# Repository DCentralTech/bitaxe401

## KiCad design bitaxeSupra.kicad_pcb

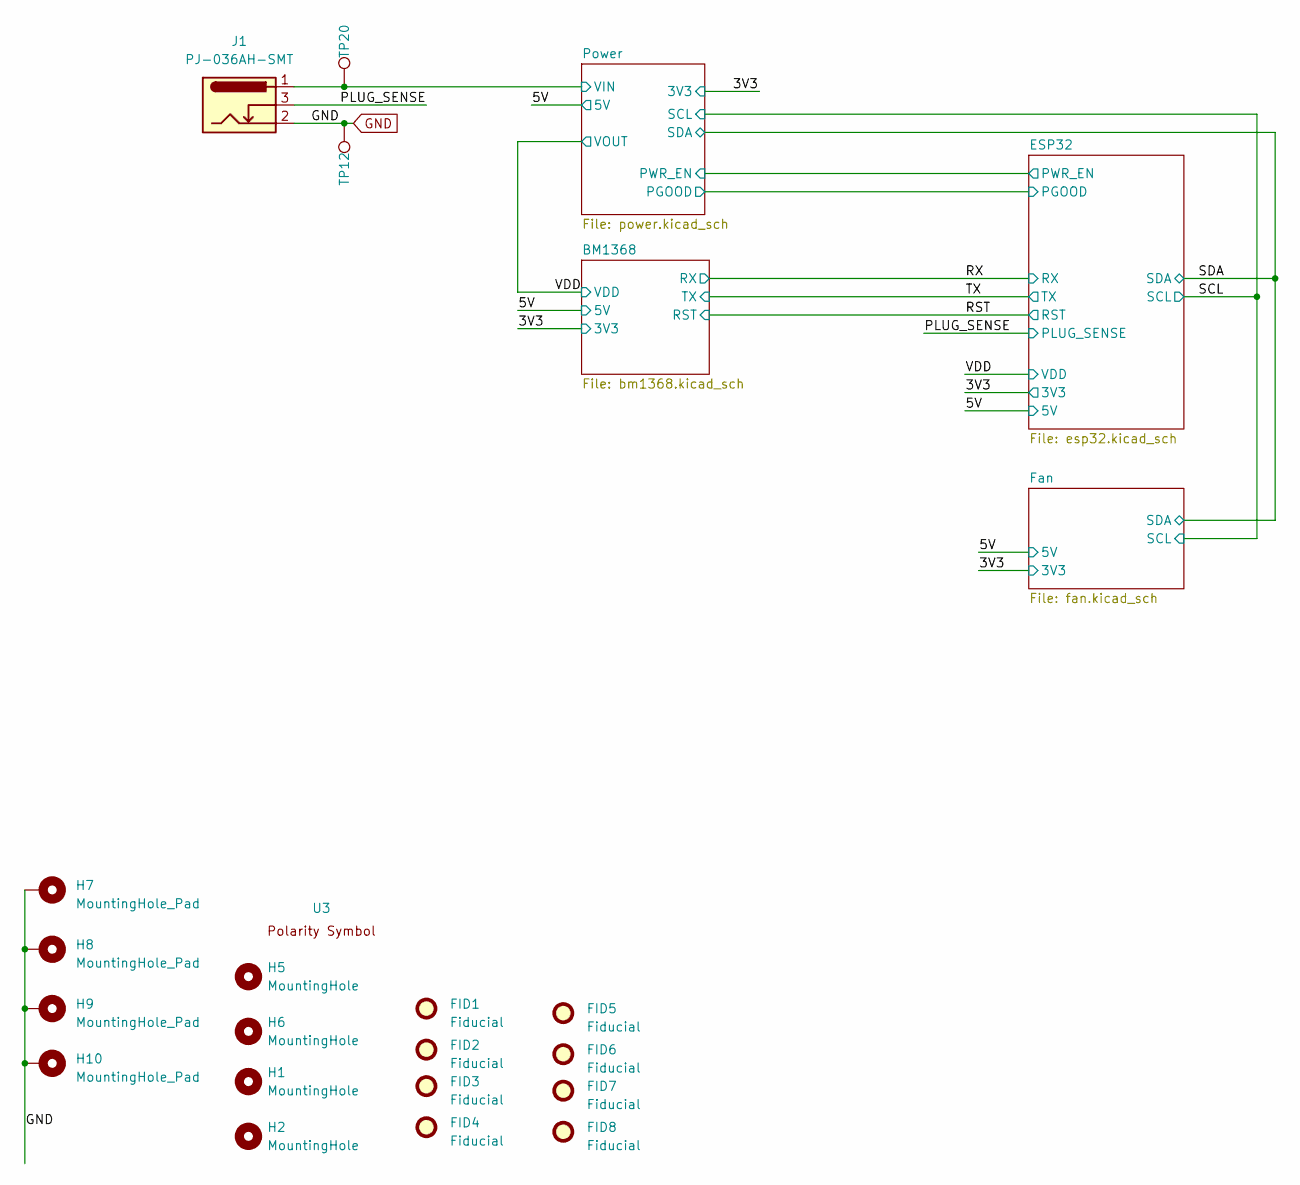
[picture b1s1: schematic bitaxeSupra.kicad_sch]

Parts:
FID1, FID2, FID3, FID4, FID5, FID6, FID7, FID8: Fiducial; Fiducial_1mm_Mask2mm
H1, H2, H5, H6: MountingHole; MountingHole_3.5mm
H7, H8, H9, H10: MountingHole_Pad; MountingHole_3mm_Pad_Via
J1: PJ-036AH-SMT; BarrelJack_CUI_PJ-036AH-SMT_Horizontal; PARTNO PJ-036AH-SMT; JLCPCB #1 C9900024875
TP12, TP20: TestPoint; TestPoint_Pad_D3.0mm
U3: polarity

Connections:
/PLUG_SENSE: J1.3; also elsewhere on the board
/Power/VIN: J1.1, TP20.1; also elsewhere on the board
GND: H7.1, H8.1, H9.1, H10.1, J1.2, TP12.1; also elsewhere on the board

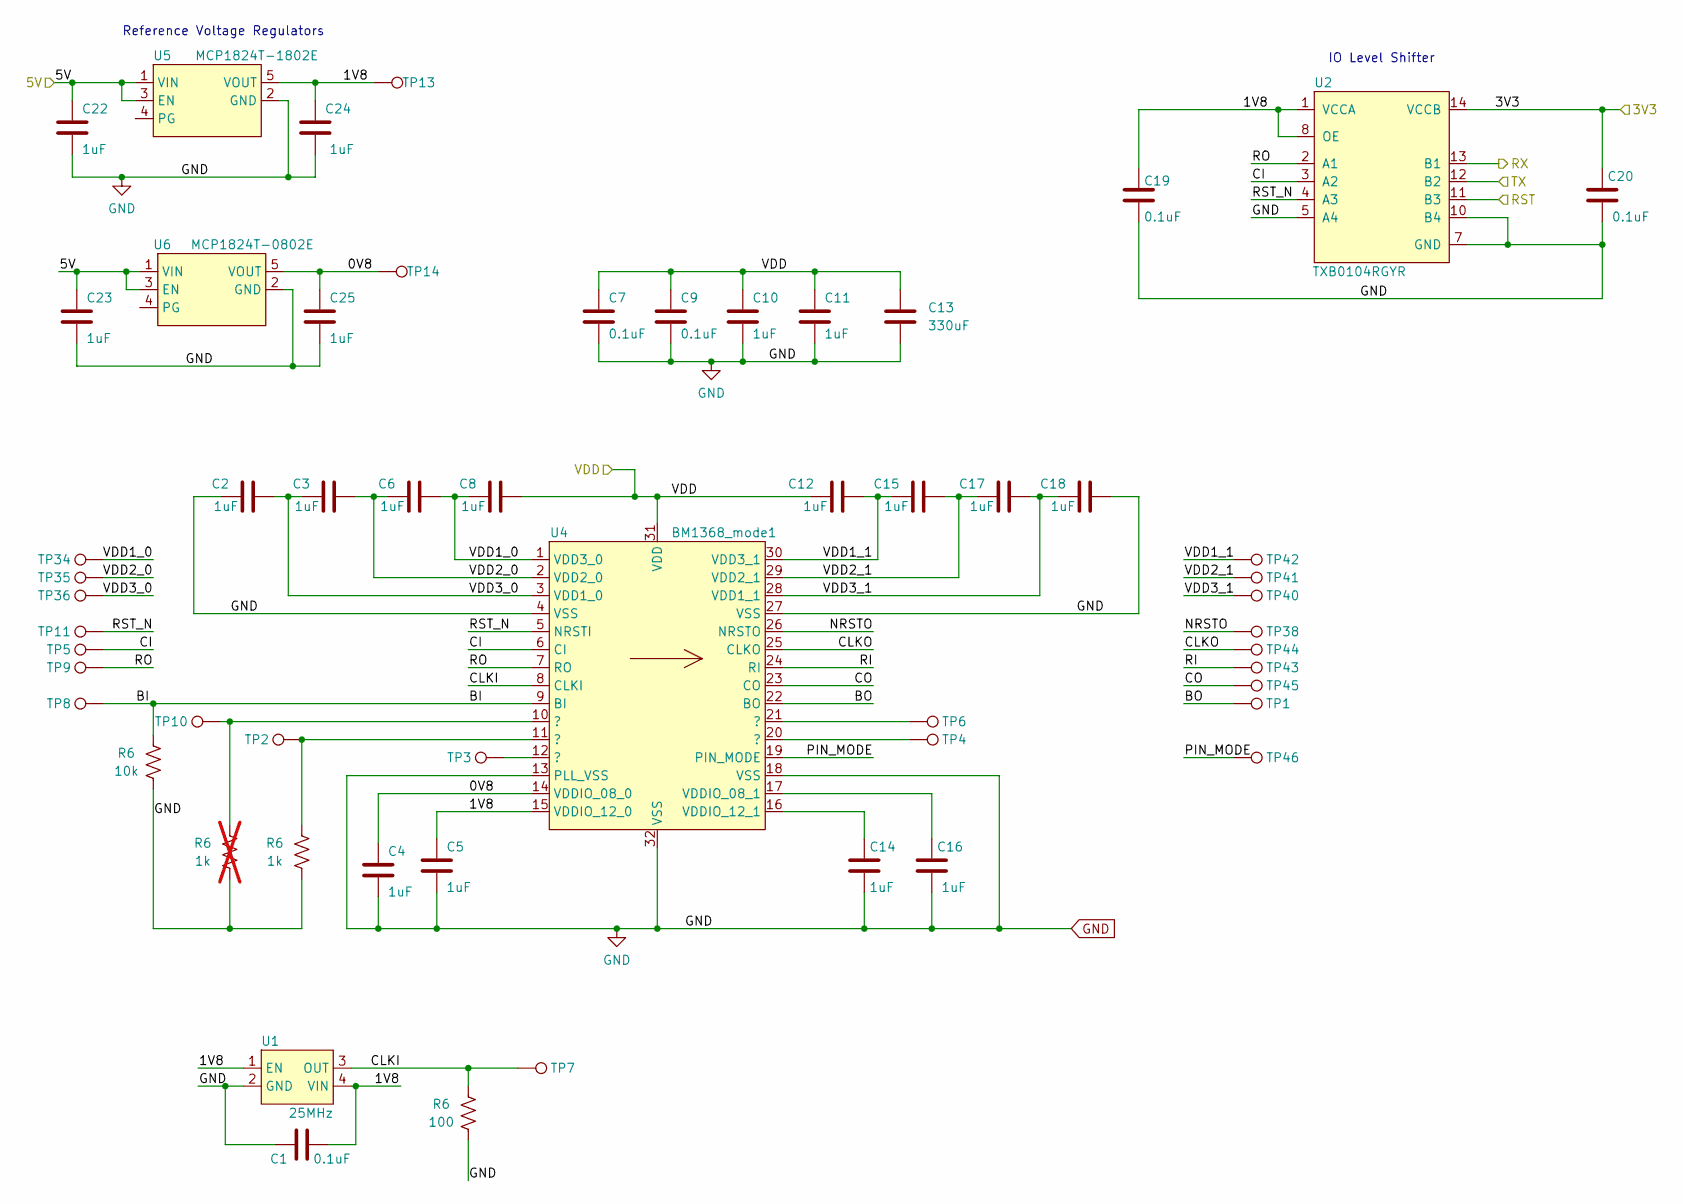
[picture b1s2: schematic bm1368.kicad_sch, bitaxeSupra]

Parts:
C1, C7, C9, C19, C20: 0.1uF; C_0402_1005Metric; PARTNO 0402X104K100CT; JLCPCB #1 C129131
C2, C3, C4, C5, C6, C8, C10, C11, C12, C14, C15, C16, C17, C18, C22, C23, C24, C25: 1uF; C_0402_1005Metric; PARTNO EMK105BJ105MV-F; JLCPCB #1 C325464
C13: 330uF; C_1210_3225Metric; PARTNO GRM32ER60G337ME05L; JLCPCB #1 C528969
R6: 1k; R_0402_1005Metric; PARTNO RC0402FR-071KL; JLCPCB #1 C106235; not fitted
TP1, TP2, TP3, TP4, TP5, TP6, TP7, TP8, TP9, TP10, TP11, TP13, TP14, TP34, TP35, TP36, TP38, TP40, TP41, TP42, TP43, TP44, TP45, TP46: TestPoint; TestPoint_Pad_D1.5mm
U1: 25MHz; O 25,0-JO32-B-1V3-1-T1-LF; PARTNO O 25,0-JO32-B-1V3-1-T1-LF; JLCPCB #1 C669088
U2: TXB0104RGYR; TXB0104; PARTNO TXB0104RGYR; JLCPCB #1 C400708
U4: BM1368_mode1; BM1368
U5: MCP1824T-1802E; SOT-23-5; PARTNO MCP1824T-1802E/OT; JLCPCB #1 C625462
U6: MCP1824T-0802E; SOT-23-5; PARTNO MCP1824T-0802E/OT; JLCPCB #1 C625460

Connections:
/3V3: C20.1, U2.14 (VCCB); also elsewhere on the board
/5V: C22.1, C23.1, U5.1 (VIN), U5.3 (EN), U6.1 (VIN), U6.3 (EN); also elsewhere on the board
/BM1368/0V8: C4.1, C25.1, TP14.1, U4.14 (VDDIO_08_0), U6.5 (VOUT)
/BM1368/1V8: C1.2, C5.1, C19.1, C24.1, TP13.1, U1.1 (EN), U1.4 (VIN), U2.1 (VCCA), U2.8 (OE), U4.15 (VDDIO_12_0), U5.5 (VOUT)
/BM1368/BO: TP1.1, U4.22 (BO)
/BM1368/CI: TP5.1, U2.3 (A2), U4.6 (CI)
/BM1368/CLKO: TP44.1, U4.25 (CLKO)
/BM1368/CO: TP45.1, U4.23 (CO)
/BM1368/NRSTO: TP38.1, U4.26 (NRSTO)
/BM1368/PIN_MODE: TP46.1, U4.19 (PIN_MODE)
/BM1368/RI: TP43.1, U4.24 (RI)
/BM1368/RO: TP9.1, U2.2 (A1), U4.7 (RO)
/BM1368/RST_N: TP11.1, U2.4 (A3), U4.5 (NRSTI)
/BM1368/VDD1_0: C6.2, C8.1, TP34.1, U4.1 (VDD3_0)
/BM1368/VDD1_1: C12.2, C15.1, TP42.1, U4.30 (VDD3_1)
/BM1368/VDD2_0: C3.2, C6.1, TP35.1, U4.2 (VDD2_0)
/BM1368/VDD2_1: C15.2, C17.1, TP41.1, U4.29 (VDD2_1)
/BM1368/VDD3_0: C2.2, C3.1, TP36.1, U4.3 (VDD1_0)
/BM1368/VDD3_1: C17.2, C18.1, TP40.1, U4.28 (VDD1_1)
/RST: U2.11 (B3); also elsewhere on the board
/RX: U2.13 (B1); also elsewhere on the board
/TX: U2.12 (B2); also elsewhere on the board
/VDD: C7.1, C8.2, C9.1, C10.1, C11.1, C12.1, C13.1, U4.31 (VDD); also elsewhere on the board
GND: C1.1, C2.1, C4.2, C5.2, C7.2, C9.2, C10.2, C11.2, C13.2, C14.2, C16.2, C18.2, C19.2, C20.2, C22.2, C23.2, C24.2, C25.2, R6.1, U1.2 (GND), U2.5 (A4), U2.7 (GND), U2.10 (B4), U2.15 (GND), U2.16 (GND), U2.17 (GND), U2.18 (GND), U2.19 (GND), U4.4 (VSS), U4.13 (PLL_VSS), U4.18 (VSS), U4.27 (VSS), U4.32 (VSS), U5.2 (GND), U6.2 (GND); also elsewhere on the board
unnamed: TP3.1, U4.12 (?)
unnamed: TP4.1, U4.20 (?)
unnamed: TP6.1, U4.21 (?)
unnamed: C16.1, U4.17 (VDDIO_08_1)
unnamed: C14.1, U4.16 (VDDIO_12_1)

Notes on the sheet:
Reference Voltage Regulators
IO Level Shifter

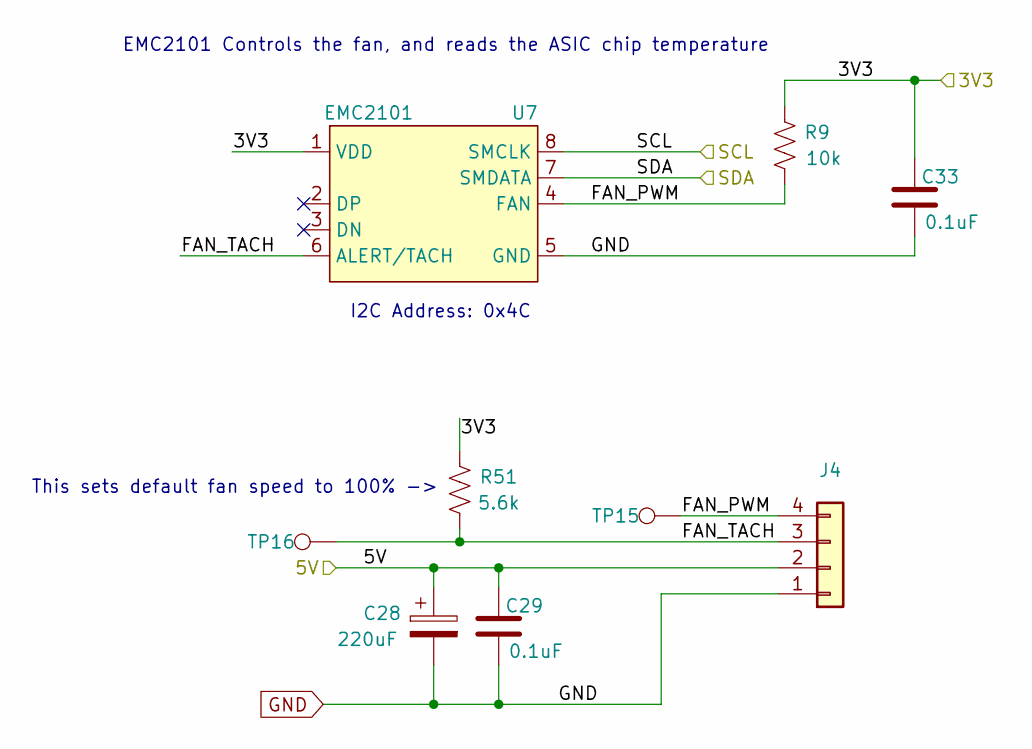
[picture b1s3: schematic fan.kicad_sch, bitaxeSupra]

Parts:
C28: 220uF; CP_Elec_6.3x7.7; PARTNO 865080345012; JLCPCB #1 C88742
C29, C33: 0.1uF; C_0402_1005Metric; PARTNO 0402X104K100CT; JLCPCB #1 C129131
J4: Conn_01x04; 470531000; PARTNO 470531000; JLCPCB #1 C492453
R9: 10k; R_0402_1005Metric; PARTNO RC0402JR-0710KL; JLCPCB #1 C60489
R51: 5.6k; R_0402_1005Metric; PARTNO RC0402FR-135K6L; JLCPCB #1 C409701
TP15, TP16: TestPoint; TestPoint_Pad_D1.5mm
U7: EMC2101; TSSOP-8_3x3mm_P0.65mm; PARTNO EMC2101-R-ACZL-TR; JLCPCB #1 C626968

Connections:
/3V3: C33.1, R9.2, U7.1 (VDD); also elsewhere on the board
/5V: C28.1, C29.1, J4.2; also elsewhere on the board
/Fan/FAN_PWM: J4.4, R9.1, TP15.1, U7.4 (FAN); also elsewhere on the board
/Fan/FAN_TACH: J4.3, TP16.1, U7.6 (ALERT/TACH); also elsewhere on the board
/SCL: U7.8 (SMCLK); also elsewhere on the board
/SDA: U7.7 (SMDATA); also elsewhere on the board
GND: C28.2, C29.2, C33.2, J4.1, U7.5 (GND); also elsewhere on the board

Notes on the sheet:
EMC2101 Controls the fan, and reads the ASIC chip temperature
This sets default fan speed to 100% ->
I2C Address: 0x4C

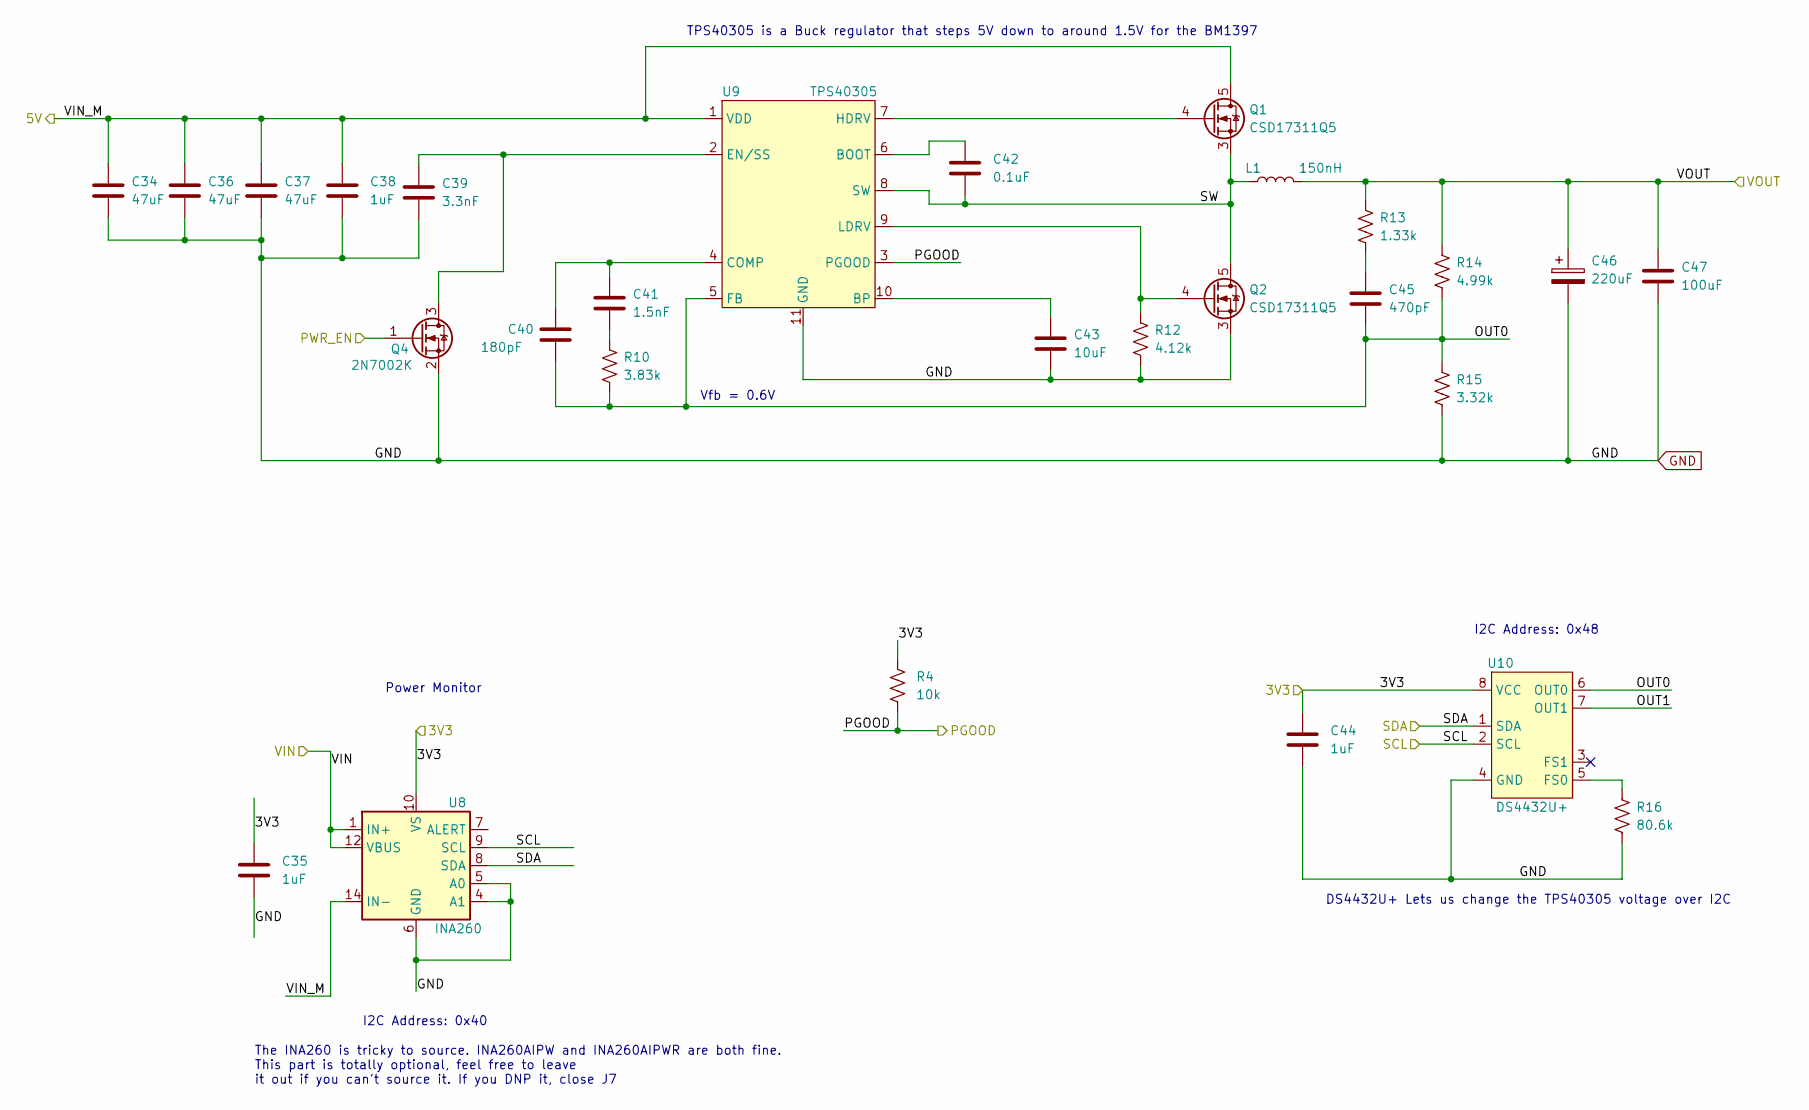
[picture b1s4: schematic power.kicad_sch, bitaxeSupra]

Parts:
C34, C36, C37: 47uF; C_1210_3225Metric; PARTNO GRM32ER61C476KE15L; JLCPCB #1 C77101
C35, C44: 1uF; C_0402_1005Metric; PARTNO EMK105BJ105MV-F; JLCPCB #1 C325464
C38: 1uF; C_0805_2012Metric; PARTNO CL21B105KOFNNNG; JLCPCB #1 C24123
C39: 3.3nF; C_0402_1005Metric; PARTNO CL05B332KB5NNNC; JLCPCB #1 C26404
C40: 180pF; C_0805_2012Metric; PARTNO CC0805JRNPO9BN181; JLCPCB #1 C458933
C41: 1.5nF; C_0805_2012Metric; PARTNO CC0805KRX7R9BB152; JLCPCB #1 C107142
C42: 0.1uF; C_0402_1005Metric; PARTNO 0402X104K100CT; JLCPCB #1 C129131
C43: 10uF; C_0805_2012Metric; PARTNO CL21A106KOQNNNE; JLCPCB #1 C1713
C45: 470pF; C_0805_2012Metric; PARTNO 0805B471K500CT; JLCPCB #1 C338123
C46: 220uF; CAP_2R5TPE220MAFB; PARTNO 2R5TPE220MAFB; JLCPCB #1 C909691
C47: 100uF; C_1206_3216Metric; PARTNO C3216X5R0J107M160AB; JLCPCB #1 C242097
L1: 150nH; FP1005R1-R15-R; PARTNO FP1005R1-R15-R; JLCPCB #1 C2923790
Q1, Q2: CSD17311Q5; PARTNO CSD17311Q5; JLCPCB #1 C139640
Q4: 2N7002K; SOT-323_SC-70; PARTNO 2N7002KW; JLCPCB #1 C266797
R4: 10k; R_0402_1005Metric; PARTNO RC0402JR-0710KL; JLCPCB #1 C60489
R10: 3.83k; R_0402_1005Metric; PARTNO RC0402FR-073K83L; JLCPCB #1 C67236
R12: 4.12k; R_0402_1005Metric; PARTNO RMCF0402FT4K12; JLCPCB #1 C60081
R13: 1.33k; R_0402_1005Metric; PARTNO RC0402FR-071K33L; JLCPCB #1 C226848
R14: 4.99k; R_0402_1005Metric; PARTNO RC0402FR-074K99L; JLCPCB #1 C25903
R15: 3.32k; R_0402_1005Metric; PARTNO RC0402FR-073K32L; JLCPCB #1 C60075
R16: 80.6k; R_0402_1005Metric; PARTNO RC0402FR-0780K6L; JLCPCB #1 C155698
U8: INA260; TSSOP-16_4.4x5mm_P0.65mm; PARTNO INA260AIPW; JLCPCB #1 C2155885
U9: TPS40305; PARTNO TPS40305DRCR; JLCPCB #1 C140285
U10: DS4432U+; TSSOP-8_3x3mm_P0.65mm; PARTNO DS4432U+; JLCPCB #1 C2679620

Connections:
/3V3: C35.1, C44.1, R4.1, U8.10 (VS), U10.8 (VCC); also elsewhere on the board
/5V: C34.1, C36.1, C37.1, C38.1, Q1.5 (D), U8.14 (IN-), U8.15 (IN-), U8.16 (IN-), U9.1 (VDD); also elsewhere on the board
/ESP32/PWR_EN: Q4.1 (G); also elsewhere on the board
/Power/OUT0: C40.2, C45.2, R10.2, R14.2, R15.1, U9.5 (FB), U10.6 (OUT0)
/Power/OUT1: U10.7 (OUT1)
/Power/PGOOD: R4.2, U9.3 (PGOOD); also elsewhere on the board
/Power/SW: C42.2, L1.1, Q1.1, Q1.2, Q1.3 (S), Q2.5 (D), U9.8 (SW)
/Power/VIN: U8.1 (IN+), U8.2 (IN+), U8.3 (IN+), U8.12 (VBUS); also elsewhere on the board
/SCL: U8.9 (SCL), U10.2 (SCL); also elsewhere on the board
/SDA: U8.8 (SDA), U10.1 (SDA); also elsewhere on the board
/VDD: C46.1, C47.1, L1.2, R13.1, R14.1; also elsewhere on the board
GND: C34.2, C35.2, C36.2, C37.2, C38.2, C39.2, C43.2, C44.2, C46.2, C47.2, Q2.1, Q2.2, Q2.3 (S), Q4.2 (S), R12.2, R15.2, R16.2, U8.4 (A1), U8.5 (A0), U8.6 (GND), U8.11 (GND), U9.11 (GND), U10.4 (GND); also elsewhere on the board
unnamed: C41.2, R10.1
unnamed: C45.1, R13.2
unnamed: Q1.4 (G), U9.7 (HDRV)
unnamed: Q2.4 (G), R12.1, U9.9 (LDRV)
unnamed: C39.1, Q4.3 (D), U9.2 (EN/SS)
unnamed: C42.1, U9.6 (BOOT)
unnamed: C43.1, U9.10 (BP)
unnamed: C40.1, C41.1, U9.4 (COMP)
unnamed: R16.1, U10.5 (FS0)

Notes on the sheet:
DS4432U+ Lets us change the TPS40305 voltage over I2C
I2C Address: 0x48
The INA260 is tricky to source. INA260AIPW and INA260AIPWR are both fine. This part is totally optional, feel free to leave it out if you can't source it. If you DNP it, close J7
Power Monitor
TPS40305 is a Buck regulator that steps 5V down to around 1.5V for the BM1397
I2C Address: 0x40
Vfb = 0.6V

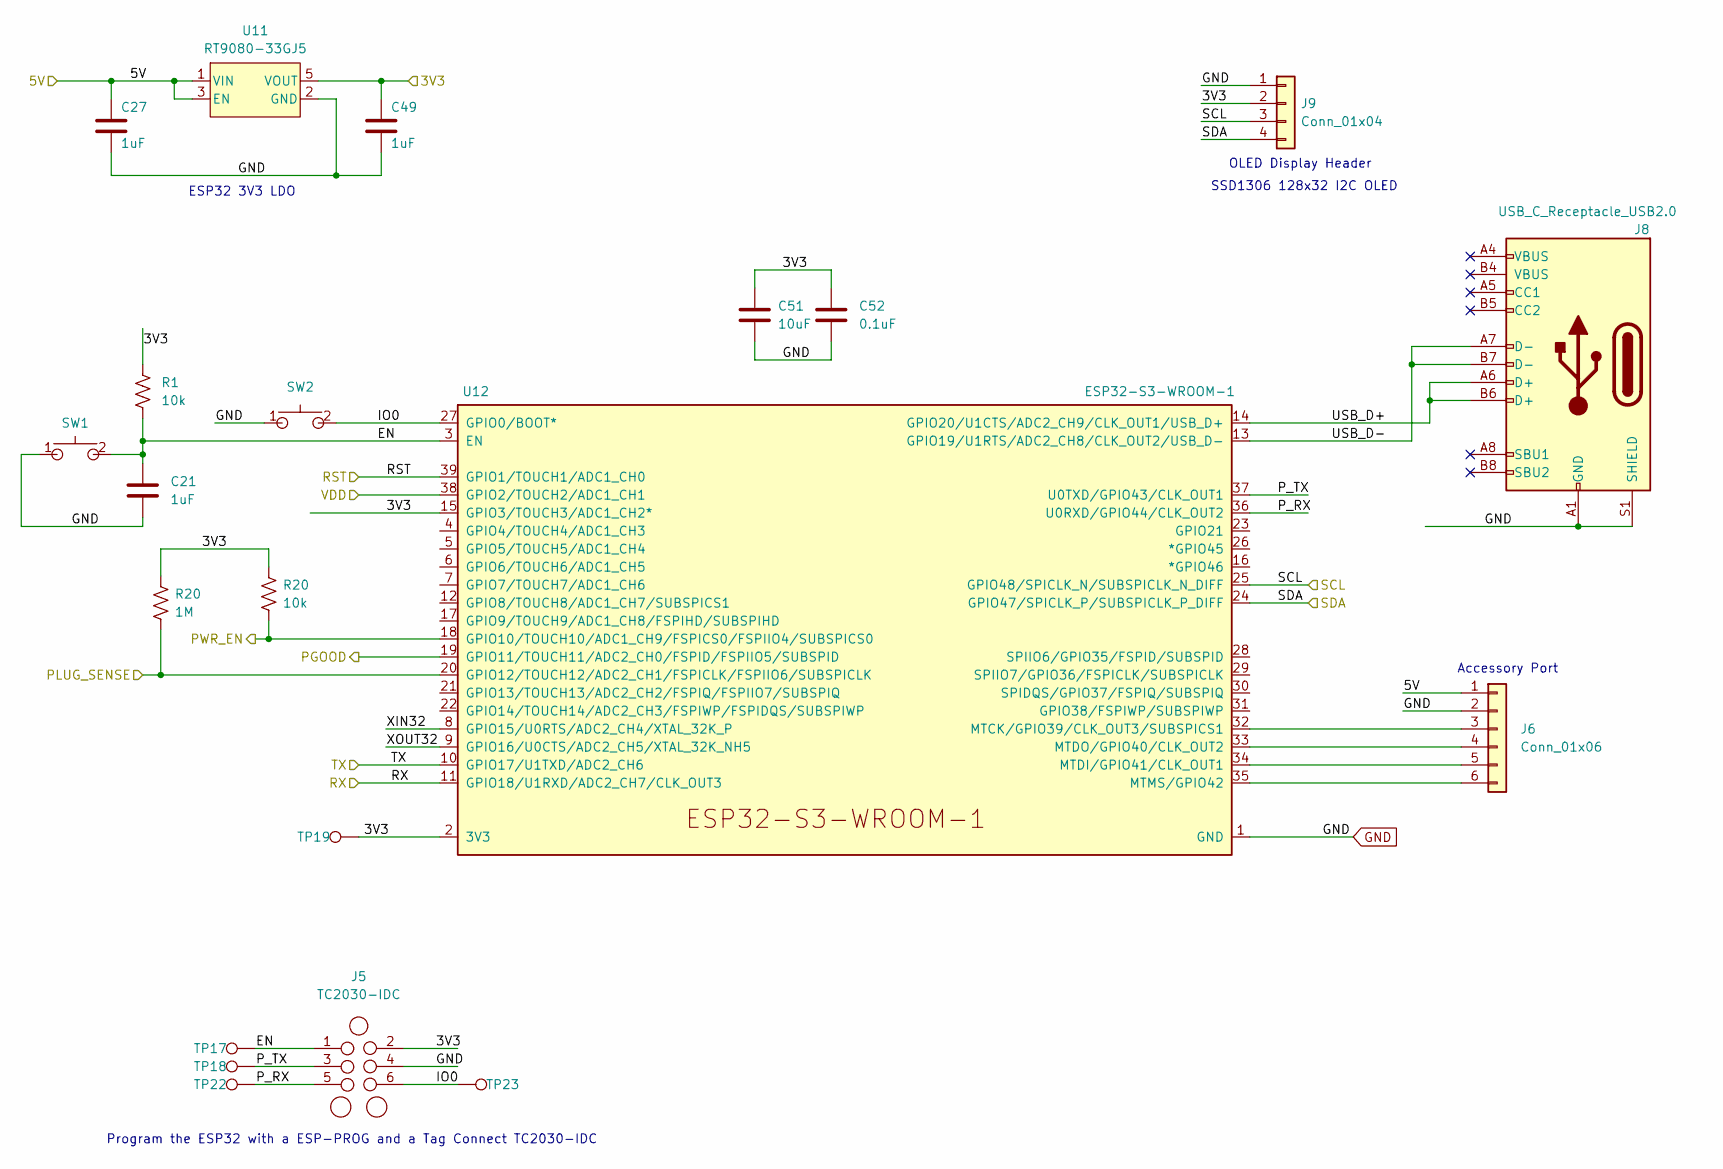
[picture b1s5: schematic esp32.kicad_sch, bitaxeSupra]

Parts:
C21, C27, C49: 1uF; C_0402_1005Metric; PARTNO EMK105BJ105MV-F; JLCPCB #1 C325464
C51: 10uF; C_0805_2012Metric; PARTNO CL21A106KOQNNNE; JLCPCB #1 C1713
C52: 0.1uF; C_0402_1005Metric; PARTNO 0402X104K100CT; JLCPCB #1 C129131
J5: TC2030-IDC; Tag-Connect_TC2030-IDC-NL_2x03_P1.27mm_Vertical
J6: Conn_01x06; PinHeader_1x06_P2.54mm_Vertical
J8: USB_C_Receptacle_USB2.0; USB_C_Receptacle_GCT_USB4105-xx-A_16P_TopMnt_Horizontal; PARTNO USB4105-GF-A; JLCPCB #1 C2982555
J9: Conn_01x04; PinHeader_1x04_P2.54mm_Vertical_shifted; PARTNO NPTC041KFXC-RC; JLCPCB #1 C2718488
R1: 10k; R_0402_1005Metric; PARTNO RC0402JR-0710KL; JLCPCB #1 C60489
R20: 1M; R_0402_1005Metric; PARTNO RC0402FR-071ML; JLCPCB #1 C138033
SW1, SW2: GT-TC029B-H025-L1N; SW_CS1213AGF260_CRS; PARTNO CS1213AGF260; JLCPCB #1 C843669
TP17, TP18, TP19, TP22, TP23: TestPoint; TestPoint_Pad_D1.5mm
U11: RT9080-33GJ5; PARTNO RT9080-33GJ5; JLCPCB #1 C841192
U12: ESP32-S3-WROOM-1; PARTNO ESP32-S3-WROOM-1-N16R8; JLCPCB #1 C2913202

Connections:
/3V3: C49.1, C51.1, C52.1, J5.2, J9.2, R1.1, TP19.1, U11.5 (VOUT), U12.2 (3V3), U12.15 (GPIO3/TOUCH3/ADC1_CH2*); also elsewhere on the board
/5V: C27.1, J6.1, U11.1 (VIN), U11.3 (EN); also elsewhere on the board
/ESP32/EN: C21.1, J5.1, R1.2, SW1.2, TP17.1, U12.3 (EN)
/ESP32/IO0: J5.6, SW2.2, TP23.1, U12.27 (GPIO0/BOOT*)
/ESP32/PWR_EN: U12.18 (GPIO10/TOUCH10/ADC1_CH9/FSPICS0/FSPIIO4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); also elsewhere on the board
/ESP32/P_RX: J5.5, TP22.1, U12.36 (U0RXD/GPIO44/CLK_OUT2)
/ESP32/P_TX: J5.3, TP18.1, U12.37 (U0TXD/GPIO43/CLK_OUT1)
/ESP32/USB_D+: J8.A6 (D+), J8.B6 (D+), U12.14 (GPIO20/U1CTS/ADC2_CH9/CLK_OUT1/USB_D+)
/ESP32/USB_D-: J8.A7 (D-), J8.B7 (D-), U12.13 (GPIO19/U1RTS/ADC2_CH8/CLK_OUT2/USB_D-)
/ESP32/XIN32: U12.8 (GPIO15/U0RTS/ADC2_CH4/XTAL_32K_P)
/ESP32/XOUT32: U12.9 (GPIO16/U0CTS/ADC2_CH5/XTAL_32K_NH5)
/PLUG_SENSE: U12.20 (GPIO12/TOUCH12/ADC2_CH1/FSPICLK/FSPIIO6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); also elsewhere on the board
/Power/PGOOD: U12.19 (GPIO11/TOUCH11/ADC2_CH0/FSPID/FSPIIO5/S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); also elsewhere on the board
/RST: U12.39 (GPIO1/TOUCH1/ADC1_CH0); also elsewhere on the board
/RX: U12.11 (GPIO18/U1RXD/ADC2_CH7/CLK_OUT3); also elsewhere on the board
/SCL: J9.3, U12.25 (GPIO48/SPICLK_N/SUBSPICLK_N_DIFF); also elsewhere on the board
/SDA: J9.4, U12.24 (GPIO47/SPICLK_P/SUBSPICLK_P_DIFF); also elsewhere on the board
/TX: U12.10 (GPIO17/U1TXD/ADC2_CH6); also elsewhere on the board
/VDD: U12.38 (GPIO2/TOUCH2/ADC1_CH1); also elsewhere on the board
GND: C21.2, C27.2, C49.2, C51.2, C52.2, J5.4, J6.2, J8.A1 (GND), J8.B1 (GND), J8.S1 (SHIELD), J9.1, SW1.1, SW2.1, U11.2 (GND), U12.1 (GND), U12.40 (GND), U12.41 (GND); also elsewhere on the board
unnamed: J6.3, U12.32 (MTCK/GPIO39/CLK_OUT3/SUBSPICS1)
unnamed: J6.4, U12.33 (MTDO/GPIO40/CLK_OUT2)
unnamed: J6.5, U12.34 (MTDI/GPIO41/CLK_OUT1)
unnamed: J6.6, U12.35 (MTMS/GPIO42)

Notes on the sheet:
Accessory Port
ESP32 3V3 LDO
Program the ESP32 with a ESP-PROG and a Tag Connect TC2030-IDC
SSD1306 128x32 I2C OLED
OLED Display Header

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
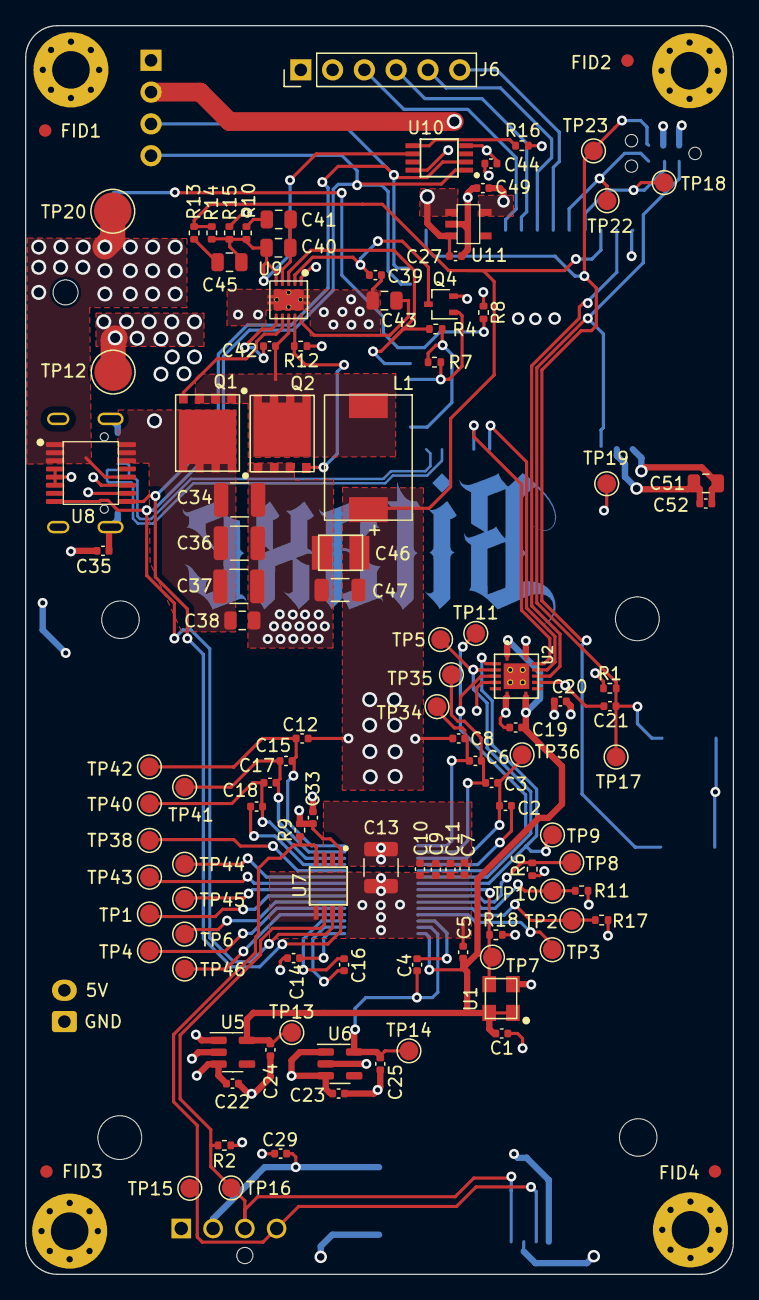
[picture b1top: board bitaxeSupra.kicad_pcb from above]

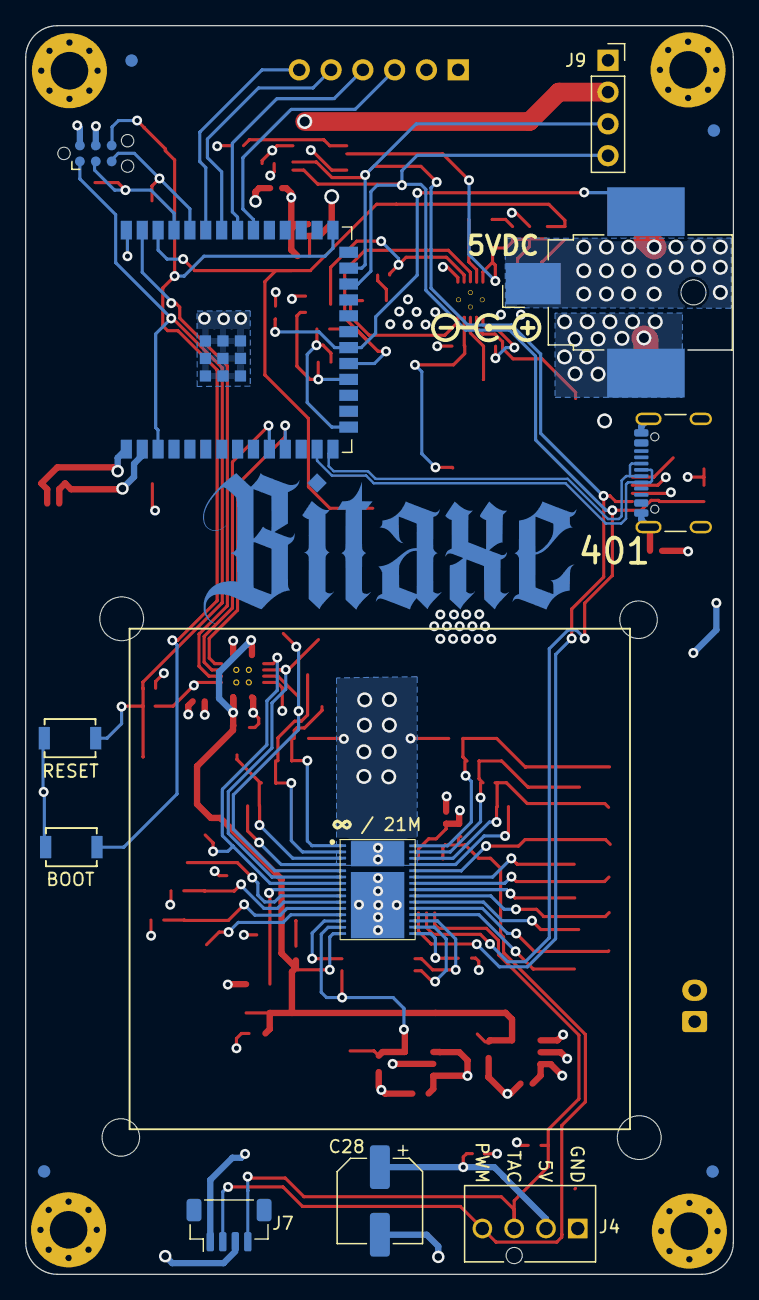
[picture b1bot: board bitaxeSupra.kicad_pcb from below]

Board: 4 copper layers, 56.5 x 99.8 mm, 137 parts (17 on the bottom side), 62 nets.

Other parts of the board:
J2: Conn_01x02; JST_XH_B2B-XH-A_1x02_P2.50mm_Vertical
J7: JST_SH_BM04B-SRSS-TB_1x04-1MP_P1.00mm_Vertical
R2: 5.6k; R_0402_1005Metric
R7: 10k; R_0402_1005Metric
R8: 1M; R_0402_1005Metric
R11, R17: 1k; R_0402_1005Metric
R18: 100; R_0402_1005Metric

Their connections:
/3V3: R2.2, R7.1, R8.1; also elsewhere on the board
/5V: J2.2 (Pin_1), J7.1; also elsewhere on the board
/ESP32/PWR_EN: R7.2; also elsewhere on the board
/Fan/FAN_PWM: J7.2; also elsewhere on the board
/Fan/FAN_TACH: J7.4, R2.1; also elsewhere on the board
/PLUG_SENSE: R8.2; also elsewhere on the board
GND: J2.1 (Pin_2), J7.3, R11.1, R17.1, R18.1; also elsewhere on the board
